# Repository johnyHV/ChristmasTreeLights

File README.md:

Christmas Tree Lights with WI-FI modul ESP-01

3D model for case
https://www.thingiverse.com/thing:5159394

Youtube video

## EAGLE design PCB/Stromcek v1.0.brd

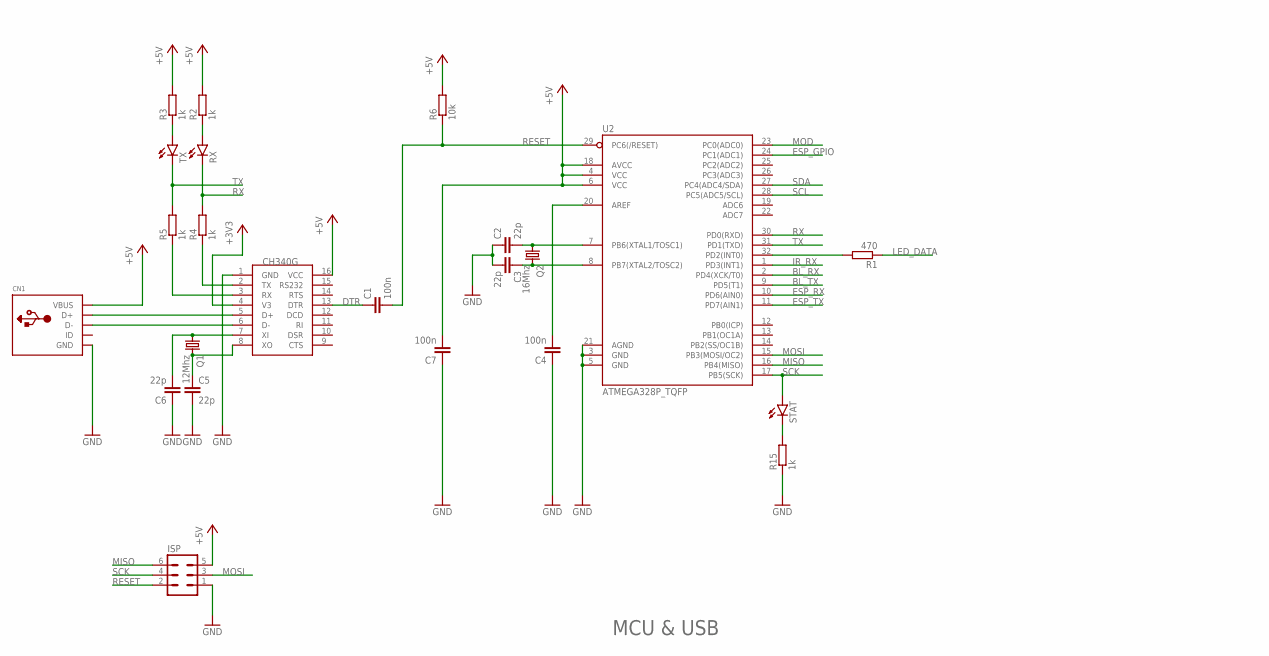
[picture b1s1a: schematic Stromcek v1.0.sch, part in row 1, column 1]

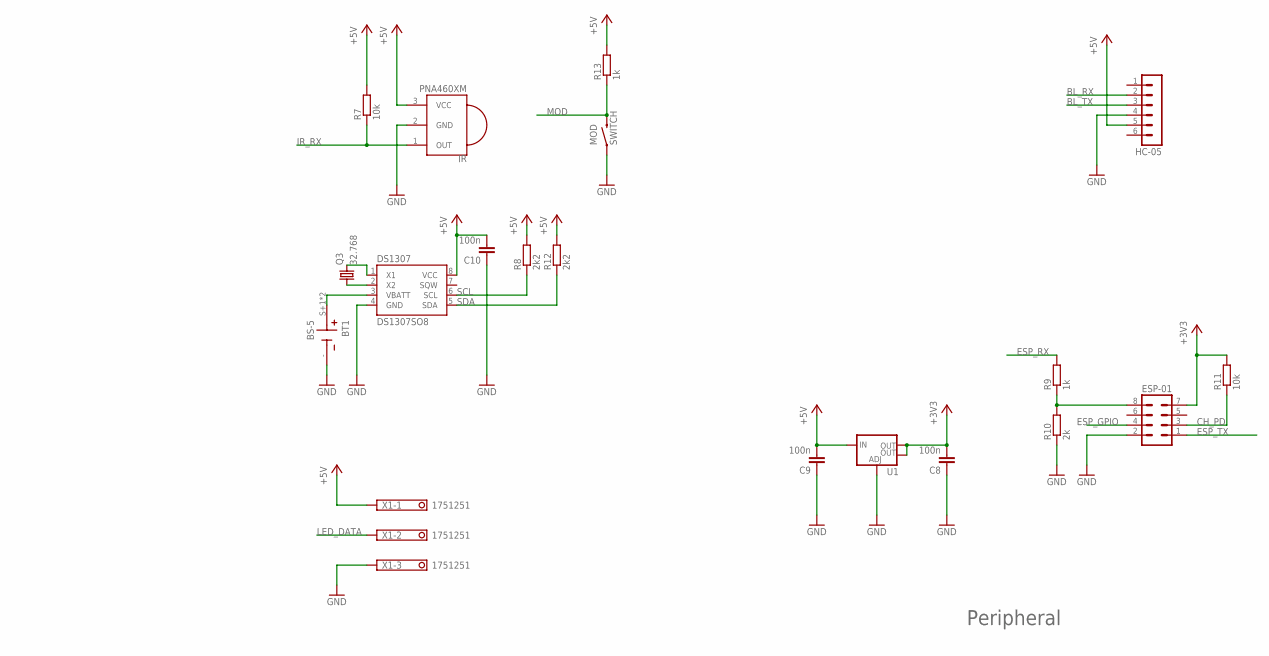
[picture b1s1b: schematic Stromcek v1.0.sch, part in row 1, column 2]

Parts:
BT1: BS-5; BAT_BS-5
C1, C4, C7, C8, C9, C10: 100n; C0603
C2, C3, C5, C6: 22p; C0603
CN1: USBMOLEX; USB-MINIB-THM-MOLEX
DS1307: DS1307SO8; SO08
ESP-01: MA04-2
HC-05: MA06-1
IR: PNA460XM
ISP: MA03-2
MOD: SWITCH; TACTILE-PTH-EZ
Q1: 12Mhz; HC49UP
Q2: 16Mhz; HC49UP
Q3: 32.768; TC26
R1: 470; R0603
R2, R3, R4, R5, R9, R13, R15: 1k; R0603
R6, R7, R11: 10k; R0603
R8, R12: 2k2; R0603
R10: 2k; R0603
RX: LEDSML0805; SML0805
STAT: LEDSML0805; SML0805
TX: LEDSML0805; SML0805
U1: V_REG_LM1117SOT223; SOT223
U2: ATMEGA328P_TQFP; TQFP32-08
U$1: CH340G; SOIC16
X1: 1751251

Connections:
+3V3: C8.2, ESP-01.7, R11.2, U1.2 (OUT), U1.4 (OUT), U$1.4 (V3)
+5V: C7.2, C9.2, C10.2, CN1.VBUS, DS1307.8 (VCC), HC-05.5, IR.3 (VCC), ISP.5, R2.2, R3.2, R6.2, R7.2, R8.2, R12.2, R13.2, U1.3 (IN), U2.4 (VCC), U2.6 (VCC), U2.18 (AVCC), U$1.16 (VCC), X1.1
BL_RX: HC-05.2, U2.2 (PD4(XCK/T0))
BL_TX: HC-05.3, U2.9 (PD5(T1))
CH_PD: ESP-01.3, R11.1
DTR: C1.1, U$1.13 (DTR)
ESP_GPIO: ESP-01.4, U2.24 (PC1(ADC1))
ESP_RX: R9.2, U2.10 (PD6(AIN0))
ESP_RX_: ESP-01.8, R9.1, R10.2
ESP_TX: ESP-01.1, U2.11 (PD7(AIN1))
GND: BT1.-, C2.1, C3.2, C4.1, C5.2, C6.1, C7.1, C8.1, C9.1, C10.1, CN1.GND, CN1.GND1 (GND), CN1.GND4 (GND), DS1307.4 (GND), ESP-01.2, HC-05.4, IR.2 (GND), ISP.1, MOD.1, R10.1, R15.1, U1.1 (ADJ), U2.3 (GND), U2.5 (GND), U2.21 (AGND), U$1.1 (GND), X1.3
IR_RX: IR.1 (OUT), R7.1, U2.1 (PD3(INT1))
LED_DATA: R1.1, X1.2
MISO: ISP.6, U2.16 (PB4(MISO))
MOD: MOD.3 (2), R13.1, U2.23 (PC0(ADC0))
MOSI: ISP.3, U2.15 (PB3(MOSI/OC2))
unnamed: CN1.D+, U$1.5 (D+)
unnamed: R1.2, U2.32 (PD2(INT0))
unnamed: CN1.D-, U$1.6 (D-)
unnamed: R5.1, U$1.3 (RX)
unnamed: R4.1, U$1.2 (TX)
unnamed: C2.2, Q2.1, U2.7 (PB6(XTAL1/TOSC1))
unnamed: C6.2, Q1.1, U$1.7 (XI)
unnamed: C5.1, Q1.2, U$1.8 (XO)
unnamed: R2.1, RX.A
unnamed: R3.1, TX.A
unnamed: C3.1, Q2.2, U2.8 (PB7(XTAL2/TOSC2))
unnamed: C4.2, U2.20 (AREF)
unnamed: R15.2, STAT.C
unnamed: BT1.S+1 (+), BT1.S+2 (+), DS1307.3 (VBATT)
unnamed: DS1307.2 (X2), Q3.1
unnamed: DS1307.1 (X1), Q3.2
RESET: C1.2, ISP.2, R6.1, U2.29 (PC6(/RESET))
RX: R4.2, RX.C, U2.30 (PD0(RXD))
SCK: ISP.4, STAT.A, U2.17 (PB5(SCK))
SCL: DS1307.6 (SCL), R8.1, U2.28 (PC5(ADC5/SCL))
SDA: DS1307.5 (SDA), R12.1, U2.27 (PC4(ADC4/SDA))
TX: R5.2, TX.C, U2.31 (PD1(TXD))

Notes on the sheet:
MCU & USB
Peripheral

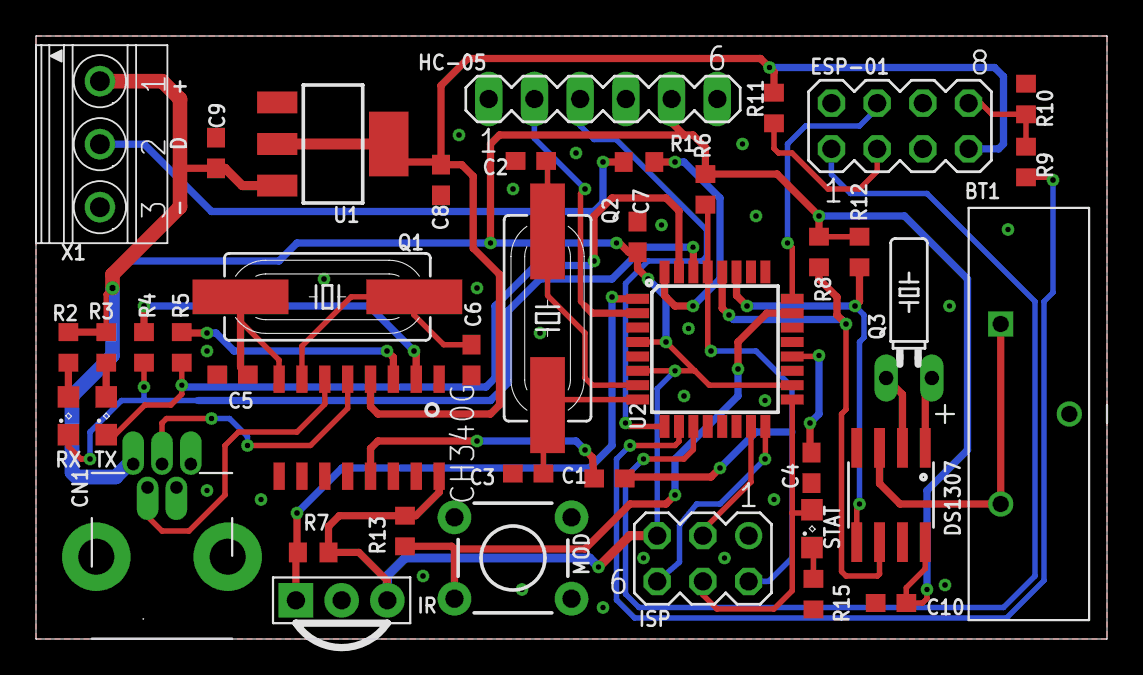
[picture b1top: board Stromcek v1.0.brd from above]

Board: 2 copper layers, 59.5 x 33.5 mm, 42 parts (0 on the bottom side), 38 nets.

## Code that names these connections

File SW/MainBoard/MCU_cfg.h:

/**
 * @file MCU_cfg.h
 *
 * @brief Konfiguracia procesora
 *
 * @author Miroslav Pivovarsky
 * Contact: miroslav.pivovarsky@gmail.com
 * 
 * @bug: no know bug
 *
 */

#ifndef __MCU_cfg_h_
#define __MCU_cfg_h_

#define SOFTWARE_VERSION              "1.0.1"     ///< verzia firmware

#define NUM_LEDS                      100         ///< pocet LED diod na LED pase
#define LED_BRIGHTNESS                255         ///< maximalny JAS led diod na LED pase
#define LED_TYPE                      WS2812B     ///< typ LED diod na LED pase
#define COLOR_ORDER                   RGB         ///< farebne spektrum LED diod

#define BLUETOOTH_ENABLE              false       ///< Zapnutie/vypnutie podpory bluetooth modulu a komunikacie s nim
#define WIFI_ENABLE                   true        ///< Zapnutie/vypnutie podpory WI-FI modulu a komunikaciu s WI-FI
#define IR_REMOTE_ENABLE              false       ///< Zapnutie/vypnutie podpory IRremote kniznice v kompilacnom procese

#define BLUETOOTH_BAUD_RATE           9600        ///< komunikacna rychlost s bluetooth modulom
#define WIFI_BAUD_RATE                9600        ///< komunikacna rychlost s modulom ESP32
#define COM_PORT_BAUD_RATE            115200      ///< komunikacna rychlost s doskou cez USB port

#define LOOP_REFRESH_TIME             1           ///< refresh time loop slucky

#define LED_STRIP_DATA_PIN            2           ///< GPIO pin pre komunikaciu s LED pasom
#define BUTTON_MODE                   14          ///< GPIO pin pre tlacidlo na zmenu efektu 
#define ESP_GPIO                      15          ///< GPIO pin pre komunikaciu s ESP modulom
#define IR_RX_INPUT                   3           ///< GPIO pin pre IR receiver
#define BLE_RX                        4           ///< GPIO pin pre SW serial s bluetooth RX
#define BLE_TX                        5           ///< GPIO pin pre SW serial s bluetooth TX
#define ESP_RX                        7           ///< GPIO pin pre SW serial s ESP32 RX
#define ESP_TX                        6           ///< GPIO pin pre SW serial s ESP32 TX
#define STATUS_LED                    13          ///< GPIO pin STATUS LED

/* EEPROM ADDRESS */
#define EEPROM_CURRENT_EFFECT         1           ///< Adresa pre ulozenie efektu ktory sa automaticky zapne pri zapnuti elektroniky

#define EEPROM_EFFECT_SPEED_HI        2           ///< Adresa pre ulozenie rychlosti blikania efektov HI bajt
#define EEPROM_EFFECT_SPEED_LOW       3           ///< Adresa pre ulozenie rychlosti blikania efektov LOW bajt

#define EEPROM_RANDOM_TIME_HI         4           ///< Adresa pre ulozenie dlzky svietenia jedneho efektu HI bajt
#define EEPROM_RANDOM_TIME_LOW        5           ///< Adresa pre ulozenie dlzky svietenia jedneho efektu HI bajt

#define EEPROM_AUTO_ON_STATUS         6           ///< Adresa pre ulozenie zapnutia/vypnutia automatickeho zapinania osvetlenia vo vybrany cas
#define EEPROM_AUTO_ON_EFFECT         7           ///< Adresa pre ulozenie efektu ktory sa zapne pri automatickom spusteni vo vybrany cas
#define EEPROM_AUTO_ON_TIME_ON_HOUR   8           ///< Adresa pre ulozenie hodiny zapnutia
#define EEPROM_AUTO_ON_TIME_ON_MIN    9           ///< Adresa pre ulozenie minut zapnutia
#define EEPROM_AUTO_ON_TIME_OFF_HOUR  10          ///< Adresa pre ulozenie hodin vypnutia
#define EEPROM_AUTO_ON_TIME_OFF_MIN   11          ///< Adresa pre ulozenie minut vypnutia

#endif

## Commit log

2020-11-29 init commit

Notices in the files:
parts and their libraries:
SparkFun-DigitalIC: Licensing: Creative Commons ShareAlike 4.0 International - https://creativecommons.org/licenses/by-sa/4.0
SparkFun: Licensing: CC v3.0 Share-Alike You are welcome to use this library for commercial purposes.
